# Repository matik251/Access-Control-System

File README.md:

# Access Control System
 Embedded system project on Espressif boards with sensors. Device consist from two modules: RFID connected to PC and supervision module that is powered by powerbank. Data obtained is transmitted to PC via USB. Additionally you can find on sd card images from camera that is triggered by PIR sensor.

|Element| Purpose|
|---|---|
|ESP-32 CAM | Esp32 with cam and SD card to take and store photos |
| PIR HC-SR501 sensor | Detects movement in environemnt of module and wakes esp from deepsleep|
| ESP8266 | Handles rfid data and sends to connected pc via USB |
| RFID PN532 sensor | Reads RFID cards and tags |

## Operation

↓↓↓ ESP8266 sends data obtained from RFID so program running on connected PC can read it (example with putty)

Sample photo from ESP32-CAM took after high-state signal from RFID →→→

## Board scheme

## Board project

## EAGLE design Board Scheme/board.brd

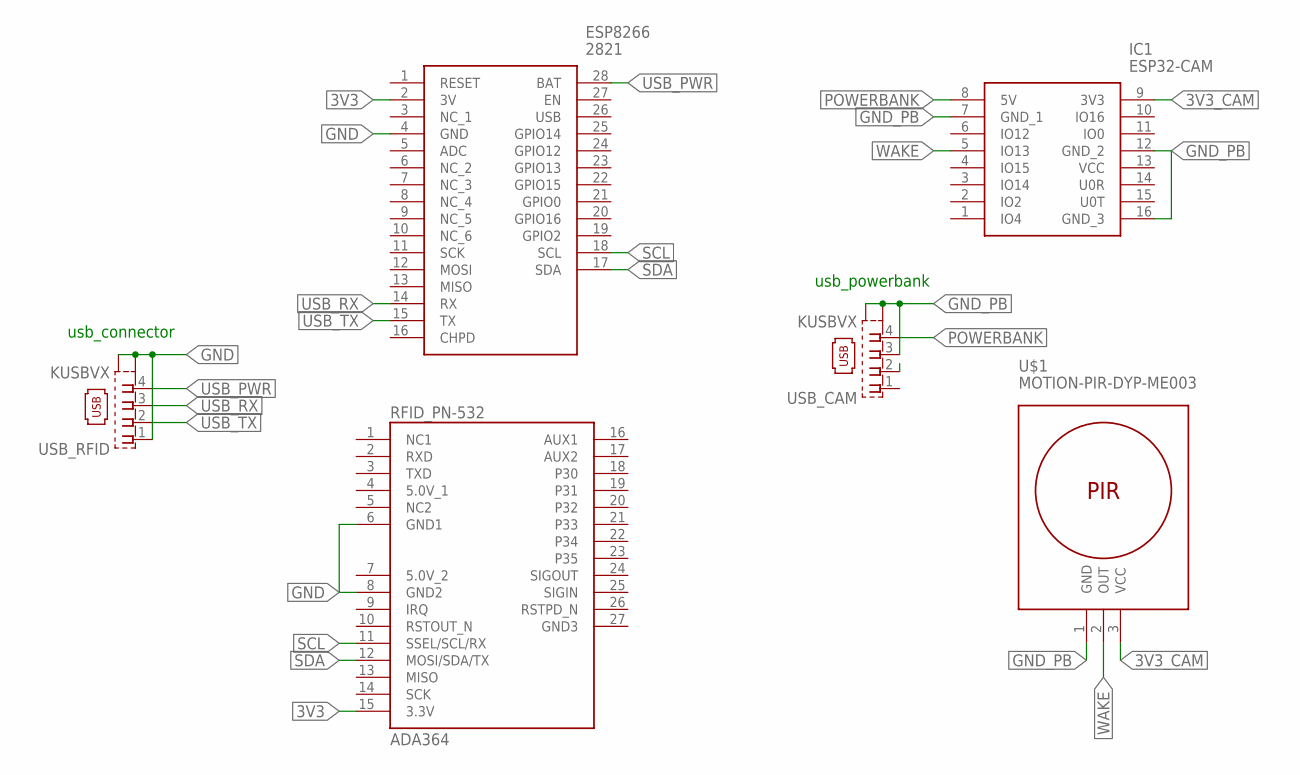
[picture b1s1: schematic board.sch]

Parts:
ESP8266: 2821
IC1: ESP32-CAM; ESP32CAM
RFID_PN-532: ADA364; ADAFRUIT_ADA364
U$1: MOTION-PIR-DYP-ME003
USB_CAM: KUSBVX
USB_RFID: KUSBVX

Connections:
3V3: ESP8266.2 (3V), RFID_PN-532.15 (3.3V)
3V3_CAM: IC1.9 (3V3), U$1.3 (VCC)
GND: ESP8266.4 (GND), RFID_PN-532.6 (GND1), RFID_PN-532.8 (GND2), USB_RFID.1, USB_RFID.M1 (S1), USB_RFID.M2 (S2)
GND_PB: IC1.7 (GND_1), IC1.12 (GND_2), IC1.16 (GND_3), U$1.1 (GND), USB_CAM.3, USB_CAM.M1 (S1), USB_CAM.M2 (S2)
unnamed: USB_CAM.1, USB_CAM.2
POWERBANK: IC1.8 (5V), USB_CAM.4
SCL: ESP8266.18 (SCL), RFID_PN-532.11 (SSEL/SCL/RX)
SDA: ESP8266.17 (SDA), RFID_PN-532.12 (MOSI/SDA/TX)
USB_PWR: ESP8266.28 (BAT), USB_RFID.4
USB_RX: ESP8266.14 (RX), USB_RFID.3
USB_TX: ESP8266.15 (TX), USB_RFID.2
WAKE: IC1.5 (IO13), U$1.2 (OUT)

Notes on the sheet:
usb_connector
usb_powerbank

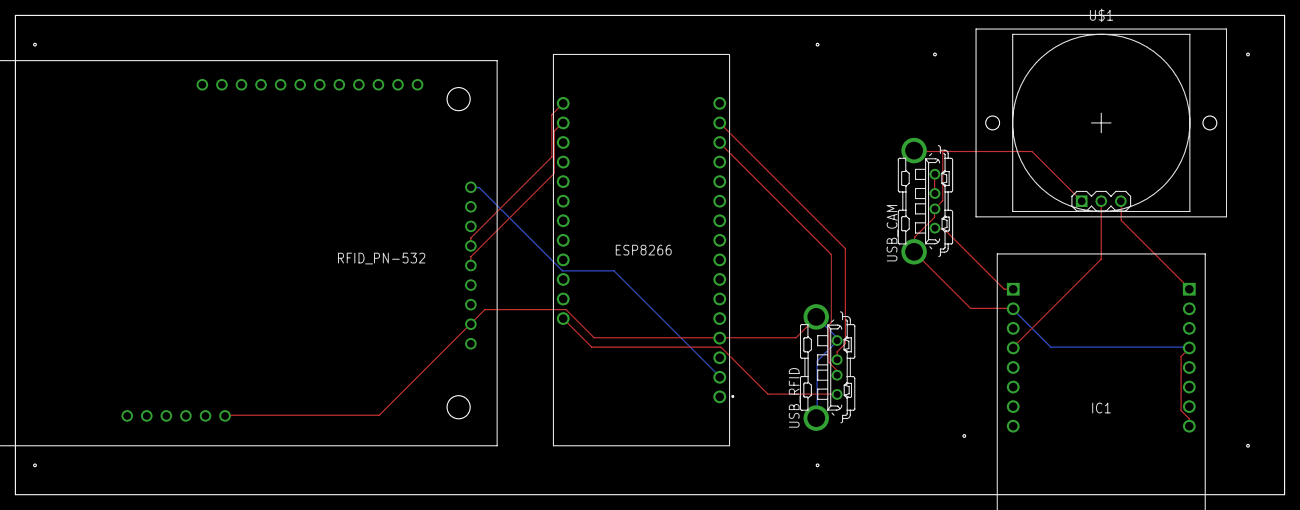
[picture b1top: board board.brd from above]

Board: 2 copper layers, 164.8 x 62.2 mm, 6 parts (0 on the bottom side), 12 nets.

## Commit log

2020-02-26 Release

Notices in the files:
parts and their libraries:
diy-modules: Released under the Creative Commons Attribution 4.0 International License: http://creativecommons.org/licenses/by/4.0
